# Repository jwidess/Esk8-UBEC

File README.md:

# Esk8-UBEC
Esk8 6-14S to 12V UBEC

This is the repository for the Esk8 UBEC by JdogAwesome. The .sch and .brd files for the UBEC are availabe for download.

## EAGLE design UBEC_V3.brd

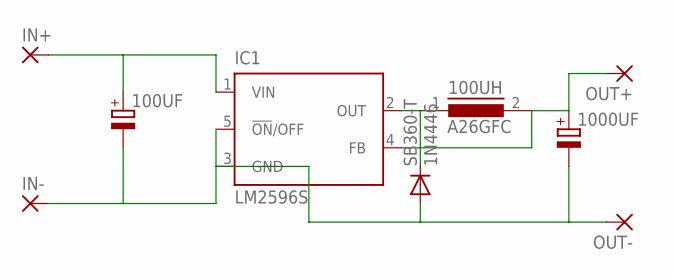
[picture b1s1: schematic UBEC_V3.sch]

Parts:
100UF: CPOL-EUE3.5-8; E3,5-8
100UH: A26GFC
1000UF: CPOL-EUE3.5-10; E3,5-10
IC1: LM2596S; TO263-5
IN+: SMD5; SMD2,54-5,08
IN-: SMD5; SMD2,54-5,08
OUT+: SMD5; SMD2,54-5,08
OUT-: SMD5; SMD2,54-5,08
SB360-T: 1N4446; DO35-10

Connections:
unnamed: 100UF.-, 1000UF.-, IC1.3 (GND), IC1.5 (!ON!/OFF), IN-.1, OUT-.1, SB360-T.A
unnamed: 100UF.+, IC1.1 (VIN), IN+.1
unnamed: 100UH.1, IC1.2 (OUT), SB360-T.C
unnamed: 100UH.2, 1000UF.+, IC1.4 (FB), OUT+.1

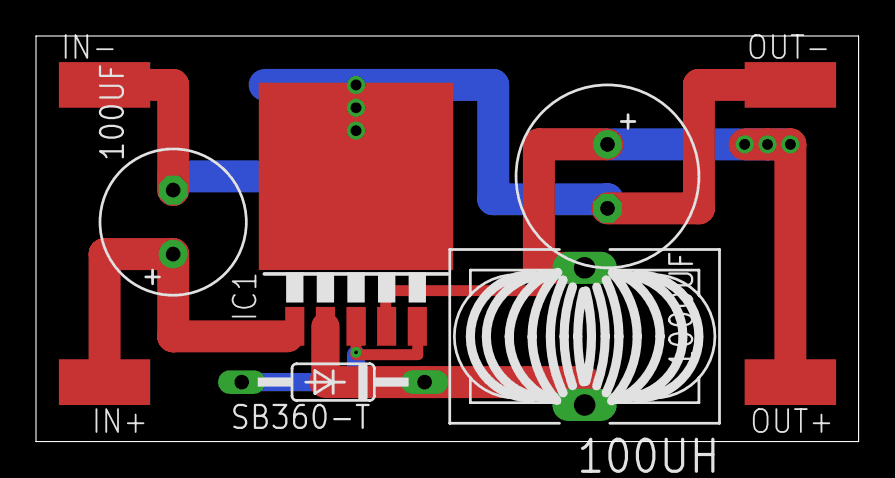
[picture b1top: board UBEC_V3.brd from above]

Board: 2 copper layers, 45.7 x 22.5 mm, 9 parts (0 on the bottom side), 4 nets.
